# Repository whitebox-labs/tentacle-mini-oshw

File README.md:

model `T2.16`

# Introduction

## What's the Tentacle Mini?
An Arduino shield to host and individually isolate up to 2 sensor circuits from Atlas Scientific to measure PH, Dissolved Oxygen, Electric Conductivity (E.C.) and Oxidation-Reduction Potential (ORP), RTD (Temperature).

* 2 channels
* 3.3V and 5V compatible
* I2C only

Individually isolated measurement circuits and communication lines prevent noise and ground loops for precise measurements.

## Getting Started
* [Documentation Site](https://www.whiteboxes.ch/docs/tentacle/t2)
* [Quick Start Tutorial](https://www.whiteboxes.ch/docs/tentacle/t2/#/quickstart)
* [How to switch EZO Circuits to I2C](https://www.whiteboxes.ch/docs/tentacle/t2/#/protocols)

## Code Examples
* [Continuous Readings](https://www.whiteboxes.ch/docs/tentacle/t2/#/continuous-example)
* [Continuous, Asynchronous Readings](https://www.whiteboxes.ch/docs/tentacle/t2/#/asynchronous-example)
* [Interactive, Bidirectional Communications](https://www.whiteboxes.ch/docs/tentacle/t2/#/interactive-example)
* [Download all examples (zip)](https://github.com/whitebox-labs/tentacle-examples/archive/master.zip)
* [Examples repository on GitHub](https://github.com/whitebox-labs/tentacle-examples)
`git clone https://github.com/whitebox-labs/tentacle-examples.git`

## Downloads
* [Tentacle Setup Sketch](https://raw.githubusercontent.com/whitebox-labs/tentacle-examples/master/arduino/tentacle-setup/tentacle_setup/tentacle_setup.ino ':target=_blank')
* [T2.16 Mechanical Drawing (PDF)](https://github.com/whitebox-labs/tentacle-mini-oshw/raw/master/hardware/mechanical/tentacle_t2_mechanical.pdf)
* [BNC Connector Mechanical Drawing (PDF)](https://github.com/whitebox-labs/tentacle/raw/master/hardware/mechanical/bnc_mechanical.pdf)
* [T2.16 Schematic (PDF)](https://github.com/whitebox-labs/tentacle-mini-oshw/raw/master/hardware/T2_mini_schematic.pdf)
* [T2.16 3D-Model (STL)](https://github.com/whitebox-labs/tentacle-mini-oshw/raw/master/hardware/mechanical/tentacle_t2.STL) ([view online](https://github.com/whitebox-labs/tentacle-mini-oshw/blob/master/hardware/mechanical/tentacle_t2.STL))
* [T2.16 3D-Model (STEP)](https://github.com/whitebox-labs/tentacle-mini-oshw/raw/master/hardware/mechanical/tentacle_t2.STEP)

## Support
For customer support, please use the [contact form](https://www.whiteboxes.ch/contact/) on our website.

If you find bug in the documentation, examples or the schematic, feel free to create an issue or even a pull request here on GitHub.

## Open Source
The Tentacle Shield is [certified](http://certificate.oshwa.org/certification-directory/) Open Source Hardware with UID CH000002. Schematics and layout are licensed under [Creative Commons BY-SA 4.0](http://creativecommons.org/licenses/by-sa/4.0/). Silkscreen graphics and the trade mark “Tentacle” are intellectual property of Whitebox Labs

* [Hardware source files on GitHub](https://github.com/whitebox-labs/tentacle-mini-oshw) `git clone https://github.com/whitebox-labs/tentacle-mini-oswh.git`

Made with 

## Buy
* From [our store](https://www.whiteboxes.ch/shop/tentacle-mini/) – we ship worldwide
* or from one of our [Distributors](https://www.whiteboxes.ch/distributors)

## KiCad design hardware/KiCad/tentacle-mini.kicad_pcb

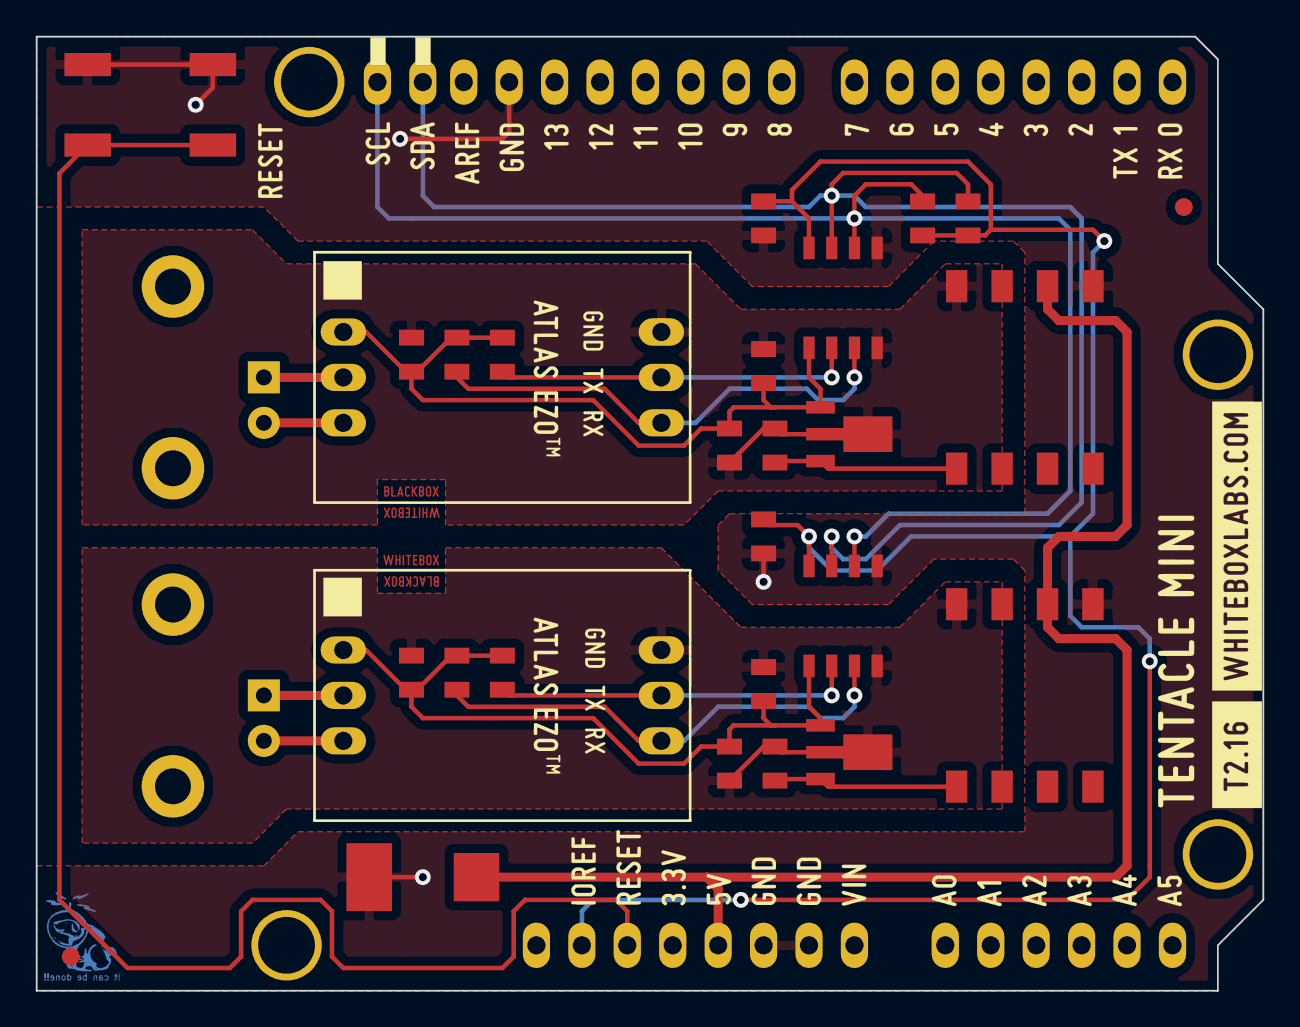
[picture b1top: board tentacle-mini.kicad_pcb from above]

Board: 2 copper layers, 68.6 x 53.3 mm, 36 parts (0 on the bottom side), 20 nets.

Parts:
C1, C2, C6, C7: 1µF; SM0805a
C3, C8: 2.2µF; SM0805a
C4, C5, C9, C10: 0.1 µF; SM0805a
C11: 470µF; c_tant_X
DCDC1, DCDC2: R1SE_0505
P1, P2: BNC; BNC-1337543a
R1, R2, R3, R4, R5, R6: 4.7K; SM0805a
REG1, REG2: LD2981ABU50TR; sot89a
SHIELD1: ARDUINO_SHIELD; ARDUINO_SHIELD_040pinsb_no_outline
SIG_ISO1, SIG_ISO2: SI8600; so-8a
STP1, STP2: ATLAS_STAMP; Atlas_Stamp_14x21
SW1: SW_PUSH; B3S-1000P
VAL: REF; mini_F.SilkS_68.5mm
VAL#2: REF; icon
VAL#3: REF; mini_B.SilkS_68.5mm_flipped
VAL#4, VAL#5: REF; blackbox
fiducial: VAL**; fiducial
fiducial#2: VAL**; fiducial

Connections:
GND: C5.1, C10.1, C11.2, DCDC1.1, DCDC2.1, SHIELD1.GND1, SHIELD1.GND2, SHIELD1.GND3, SIG_ISO1.5, SIG_ISO2.5, SW1.1
GND_ISO1: C1.1, C2.1, C3.2, C4.1, DCDC1.4, REG1.2, SIG_ISO1.4, STP1.1
GND_ISO2: C6.1, C7.1, C8.2, C9.1, DCDC2.4, REG2.2, SIG_ISO2.4, STP2.1
unnamed: SHIELD1.RST, SW1.2
unnamed: C2.2, DCDC1.5, REG1.3
unnamed: C7.2, DCDC2.5, REG2.3
unnamed: R2.2, SIG_ISO1.2, STP1.2
unnamed: R6.1, SHIELD1.SDA, SIG_ISO1.7, SIG_ISO2.7
unnamed: R4.2, SIG_ISO2.2, STP2.2
unnamed: R3.2, SIG_ISO2.3, STP2.3
unnamed: R1.2, SIG_ISO1.3, STP1.3
unnamed: R5.1, SHIELD1.SCL, SIG_ISO1.6, SIG_ISO2.6
unnamed: P1.2, STP1.6
unnamed: P1.1, STP1.5
unnamed: P2.2, STP2.6
unnamed: P2.1, STP2.5
VCC: C11.1, DCDC1.2, DCDC2.2, SHIELD1.5V
VCOM: C5.2, C10.2, R5.2, R6.2, SHIELD1.IORE, SIG_ISO1.8, SIG_ISO2.8
V_ISO1: C1.2, C3.1, C4.2, R1.1, R2.1, REG1.1, SIG_ISO1.1, STP1.4
V_ISO2: C6.2, C8.1, C9.2, R3.1, R4.1, REG2.1, SIG_ISO2.1, STP2.4

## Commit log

2016-07-04 Initial public commit
2016-07-04 added bom and pdf schematics
2017-08-21 bom updated
2017-08-21 csv error fixed
2017-08-21 removed silkscreen gerbers
2017-08-21 added detailed 2d-drawing and 3d model
2018-08-25 added STEP 3D model
2018-09-21 zipped STEP model for easier download
2021-11-10 Update README.md
    https://forum.kicad.info/t/warning-avoid-all-links-to-kicad-pcb-org-use-kicad-org/31521
